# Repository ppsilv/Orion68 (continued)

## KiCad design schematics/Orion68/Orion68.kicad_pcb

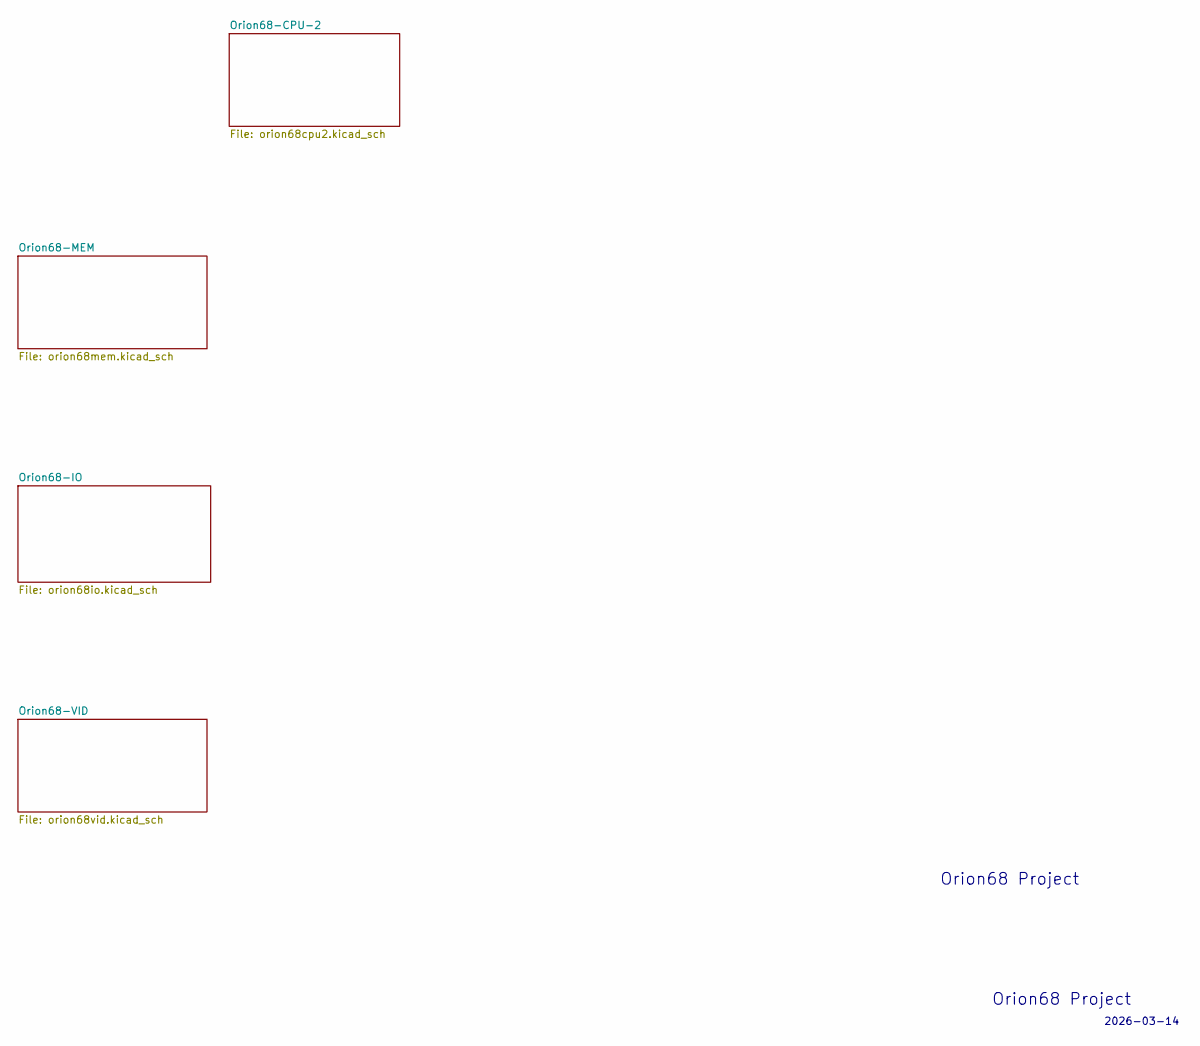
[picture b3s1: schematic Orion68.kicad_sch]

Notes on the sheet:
2026-03-14
Orion68 Project

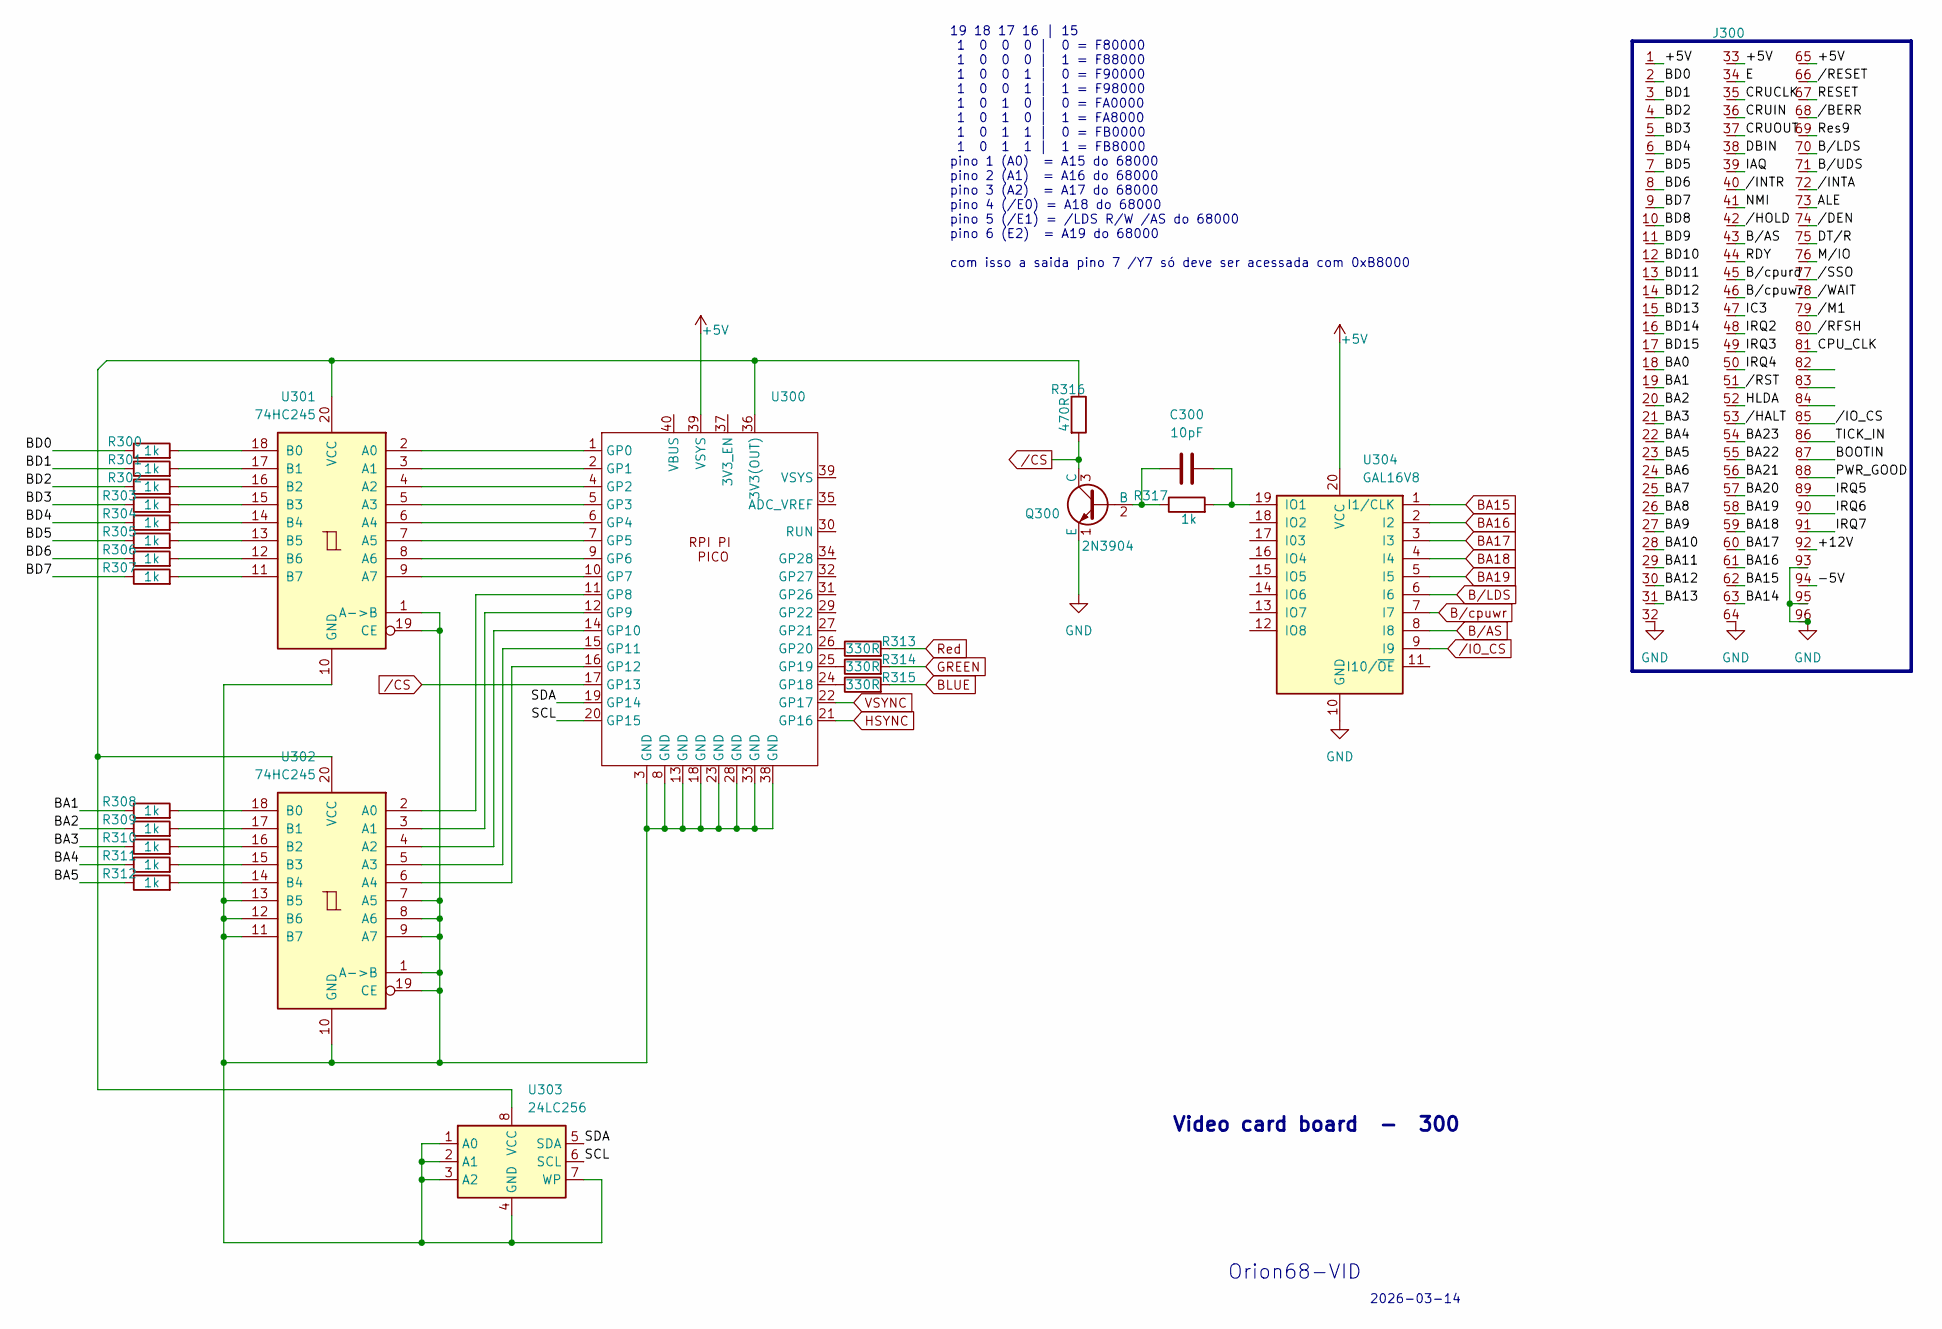
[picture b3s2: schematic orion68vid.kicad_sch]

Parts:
C300: 10pF; C_Disc_D4.3mm_W1.9mm_P5.00mm
J300: Euro96pin; conn_euro96
Q300: 2N3904; TO-92_Inline
R300, R301, R302, R303, R304, R305, R306, R307, R308, R309, R310, R311, R312, R317: 1k; R_Axial_DIN0204_L3.6mm_D1.6mm_P5.08mm_Horizontal
R313, R314, R315: 330R; R_Axial_DIN0204_L3.6mm_D1.6mm_P5.08mm_Horizontal
R316: 470R; R_Axial_DIN0204_L3.6mm_D1.6mm_P5.08mm_Horizontal
U300: DIP-40_W15.24mm
U301, U302: 74HC245; DIP-20_W7.62mm
U303: 24LC256; DIP-8_W7.62mm
U304: GAL16V8; DIP-20_W7.62mm

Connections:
+5V: J300.1, J300.33, J300.65, U300.39 (VSYS), U304.20 (VCC); also elsewhere on the board
/Orion68-VID/+12V: J300.92
/Orion68-VID/-5V: J300.94
/Orion68-VID/ALE: J300.73
/Orion68-VID/BA0: J300.18
/Orion68-VID/BA1: J300.19, R308.1
/Orion68-VID/BA2: J300.20, R309.1
/Orion68-VID/BA3: J300.21, R310.1
/Orion68-VID/BA4: J300.22, R311.1
/Orion68-VID/BA5: J300.23, R312.1
/Orion68-VID/BA6: J300.24
/Orion68-VID/BA7: J300.25
/Orion68-VID/BA8: J300.26
/Orion68-VID/BA9: J300.27
/Orion68-VID/BA10: J300.28
/Orion68-VID/BA11: J300.29
/Orion68-VID/BA12: J300.30
/Orion68-VID/BA13: J300.31
/Orion68-VID/BA14: J300.63
/Orion68-VID/BA20: J300.57
/Orion68-VID/BA21: J300.56
/Orion68-VID/BA22: J300.55
/Orion68-VID/BA23: J300.54
/Orion68-VID/BD0: J300.2, R300.1
/Orion68-VID/BD1: J300.3, R301.1
/Orion68-VID/BD2: J300.4, R302.1
/Orion68-VID/BD3: J300.5, R303.1
/Orion68-VID/BD4: J300.6, R304.1
/Orion68-VID/BD5: J300.7, R305.1
/Orion68-VID/BD6: J300.8, R306.1
/Orion68-VID/BD7: J300.9, R307.1
/Orion68-VID/BD8: J300.10
/Orion68-VID/BD9: J300.11
/Orion68-VID/BD10: J300.12
/Orion68-VID/BD11: J300.13
/Orion68-VID/BD12: J300.14
/Orion68-VID/BD13: J300.15
/Orion68-VID/BD14: J300.16
/Orion68-VID/BD15: J300.17
/Orion68-VID/BOOTIN: J300.87
/Orion68-VID/B/UDS: J300.71
/Orion68-VID/B/cpurd: J300.45
/Orion68-VID/CPU_CLK: J300.81
/Orion68-VID/CRUCLK: J300.35
/Orion68-VID/CRUIN: J300.36
/Orion68-VID/CRUOUT: J300.37
/Orion68-VID/DBIN: J300.38
/Orion68-VID/DT/R: J300.75
/Orion68-VID/E: J300.34
/Orion68-VID/HLDA: J300.52
/Orion68-VID/IAQ: J300.39
/Orion68-VID/IC3: J300.47
/Orion68-VID/IRQ2: J300.48
/Orion68-VID/IRQ3: J300.49
/Orion68-VID/IRQ4: J300.50
/Orion68-VID/IRQ5: J300.89
/Orion68-VID/IRQ6: J300.90
/Orion68-VID/IRQ7: J300.91
/Orion68-VID/M/IO: J300.76
/Orion68-VID/NMI: J300.41
/Orion68-VID/PWR_GOOD: J300.88
/Orion68-VID/RDY: J300.44
/Orion68-VID/RESET: J300.67
/Orion68-VID/Res9: J300.69
/Orion68-VID/SCL: U300.20 (GP15), U303.6 (SCL)
/Orion68-VID/SDA: U300.19 (GP14), U303.5 (SDA)
/Orion68-VID/TICK_IN: J300.86
/Orion68-VID//BERR: J300.68
/Orion68-VID//DEN: J300.74
/Orion68-VID//HALT: J300.53
/Orion68-VID//HOLD: J300.42
/Orion68-VID//INTA: J300.72
/Orion68-VID//INTR: J300.40
/Orion68-VID//M1: J300.79
/Orion68-VID//RESET: J300.66
/Orion68-VID//RFSH: J300.80
/Orion68-VID//RST: J300.51
/Orion68-VID//SSO: J300.77
/Orion68-VID//WAIT: J300.78
BA15: J300.62, U304.1 (I1/CLK)
BA16: J300.61, U304.2 (I2)
BA17: J300.60, U304.3 (I3)
BA18: J300.59, U304.4 (I4)
BA19: J300.58, U304.5 (I5)
BLUE: R315.2
B/AS: J300.43, U304.8 (I8)
B/LDS: J300.70, U304.6 (I6)
B/cpuwr: J300.46, U304.7 (I7)
GND: J300.32, J300.64, J300.93, J300.95, J300.96, Q300.1 (E), U304.10 (GND); also elsewhere on the board
GREEN: R314.2
HSYNC: U300.21 (GP16)
unnamed: C300.1, Q300.2 (B), R317.1
unnamed: R316.1, U300.36 (3V3(OUT)), U301.20 (VCC), U302.20 (VCC), U303.8 (VCC)
unnamed: U300.1 (GP0), U301.2 (A0)
unnamed: U300.2 (GP1), U301.3 (A1)
unnamed: U300.4 (GP2), U301.4 (A2)
unnamed: U300.5 (GP3), U301.5 (A3)
unnamed: U300.6 (GP4), U301.6 (A4)
unnamed: U300.7 (GP5), U301.7 (A5)
unnamed: U300.9 (GP6), U301.8 (A6)
unnamed: U300.10 (GP7), U301.9 (A7)
unnamed: U300.11 (GP8), U302.2 (A0)
unnamed: U300.12 (GP9), U302.3 (A1)
unnamed: U300.14 (GP10), U302.4 (A2)
unnamed: U300.15 (GP11), U302.5 (A3)
unnamed: U300.16 (GP12), U302.6 (A4)
unnamed: R315.1, U300.24 (GP18)
unnamed: R314.1, U300.25 (GP19)
unnamed: R313.1, U300.26 (GP20)
unnamed: U300.3 (GND), U300.8 (GND), U300.13 (GND), U300.18 (GND), U300.23 (GND), U300.28 (GND), U300.33 (GND), U300.38 (GND), U301.1 (A->B), U301.10 (GND), U301.19 (CE), U302.1 (A->B), U302.7 (A5), U302.8 (A6), U302.9 (A7), U302.10 (GND), U302.11 (B7), U302.12 (B6), U302.13 (B5), U302.19 (CE), U303.1 (A0), U303.2 (A1), U303.3 (A2), U303.4 (GND), U303.7 (WP)
unnamed: R300.2, U301.18 (B0)
unnamed: R301.2, U301.17 (B1)
unnamed: R302.2, U301.16 (B2)
unnamed: R303.2, U301.15 (B3)
unnamed: R304.2, U301.14 (B4)
unnamed: R305.2, U301.13 (B5)
unnamed: R306.2, U301.12 (B6)
unnamed: R307.2, U301.11 (B7)
unnamed: R308.2, U302.18 (B0)
unnamed: R309.2, U302.17 (B1)
unnamed: R310.2, U302.16 (B2)
unnamed: R311.2, U302.15 (B3)
unnamed: R312.2, U302.14 (B4)
unnamed: C300.2, R317.2, U304.19 (IO1)
Red: R313.2
VSYNC: U300.22 (GP17)
/CS: Q300.3 (C), R316.2, U300.17 (GP13)
/IO_CS: J300.85, U304.9 (I9)

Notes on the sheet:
2026-03-14
19 18 17 16 | 15 1 0 0 0 | 0 = F80000 1 0 0 0 | 1 = F88000 1 0 0 1 | 0 = F90000 1 0 0 1 | 1 = F98000 1 0 1 0 | 0 = FA0000 1 0 1 0 | 1 = FA8000 1 0 1 1 | 0 = FB0000 1 0 1 1 | 1 = FB8000 pino 1 (A0) = A15 do 68000 pino 2 (A1) = A16 do 68000 pino 3 (A2) = A17 do 68000 pino 4 (/E0) = A18 do 68000 pino 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
Orion68-VID
Video card board - 300

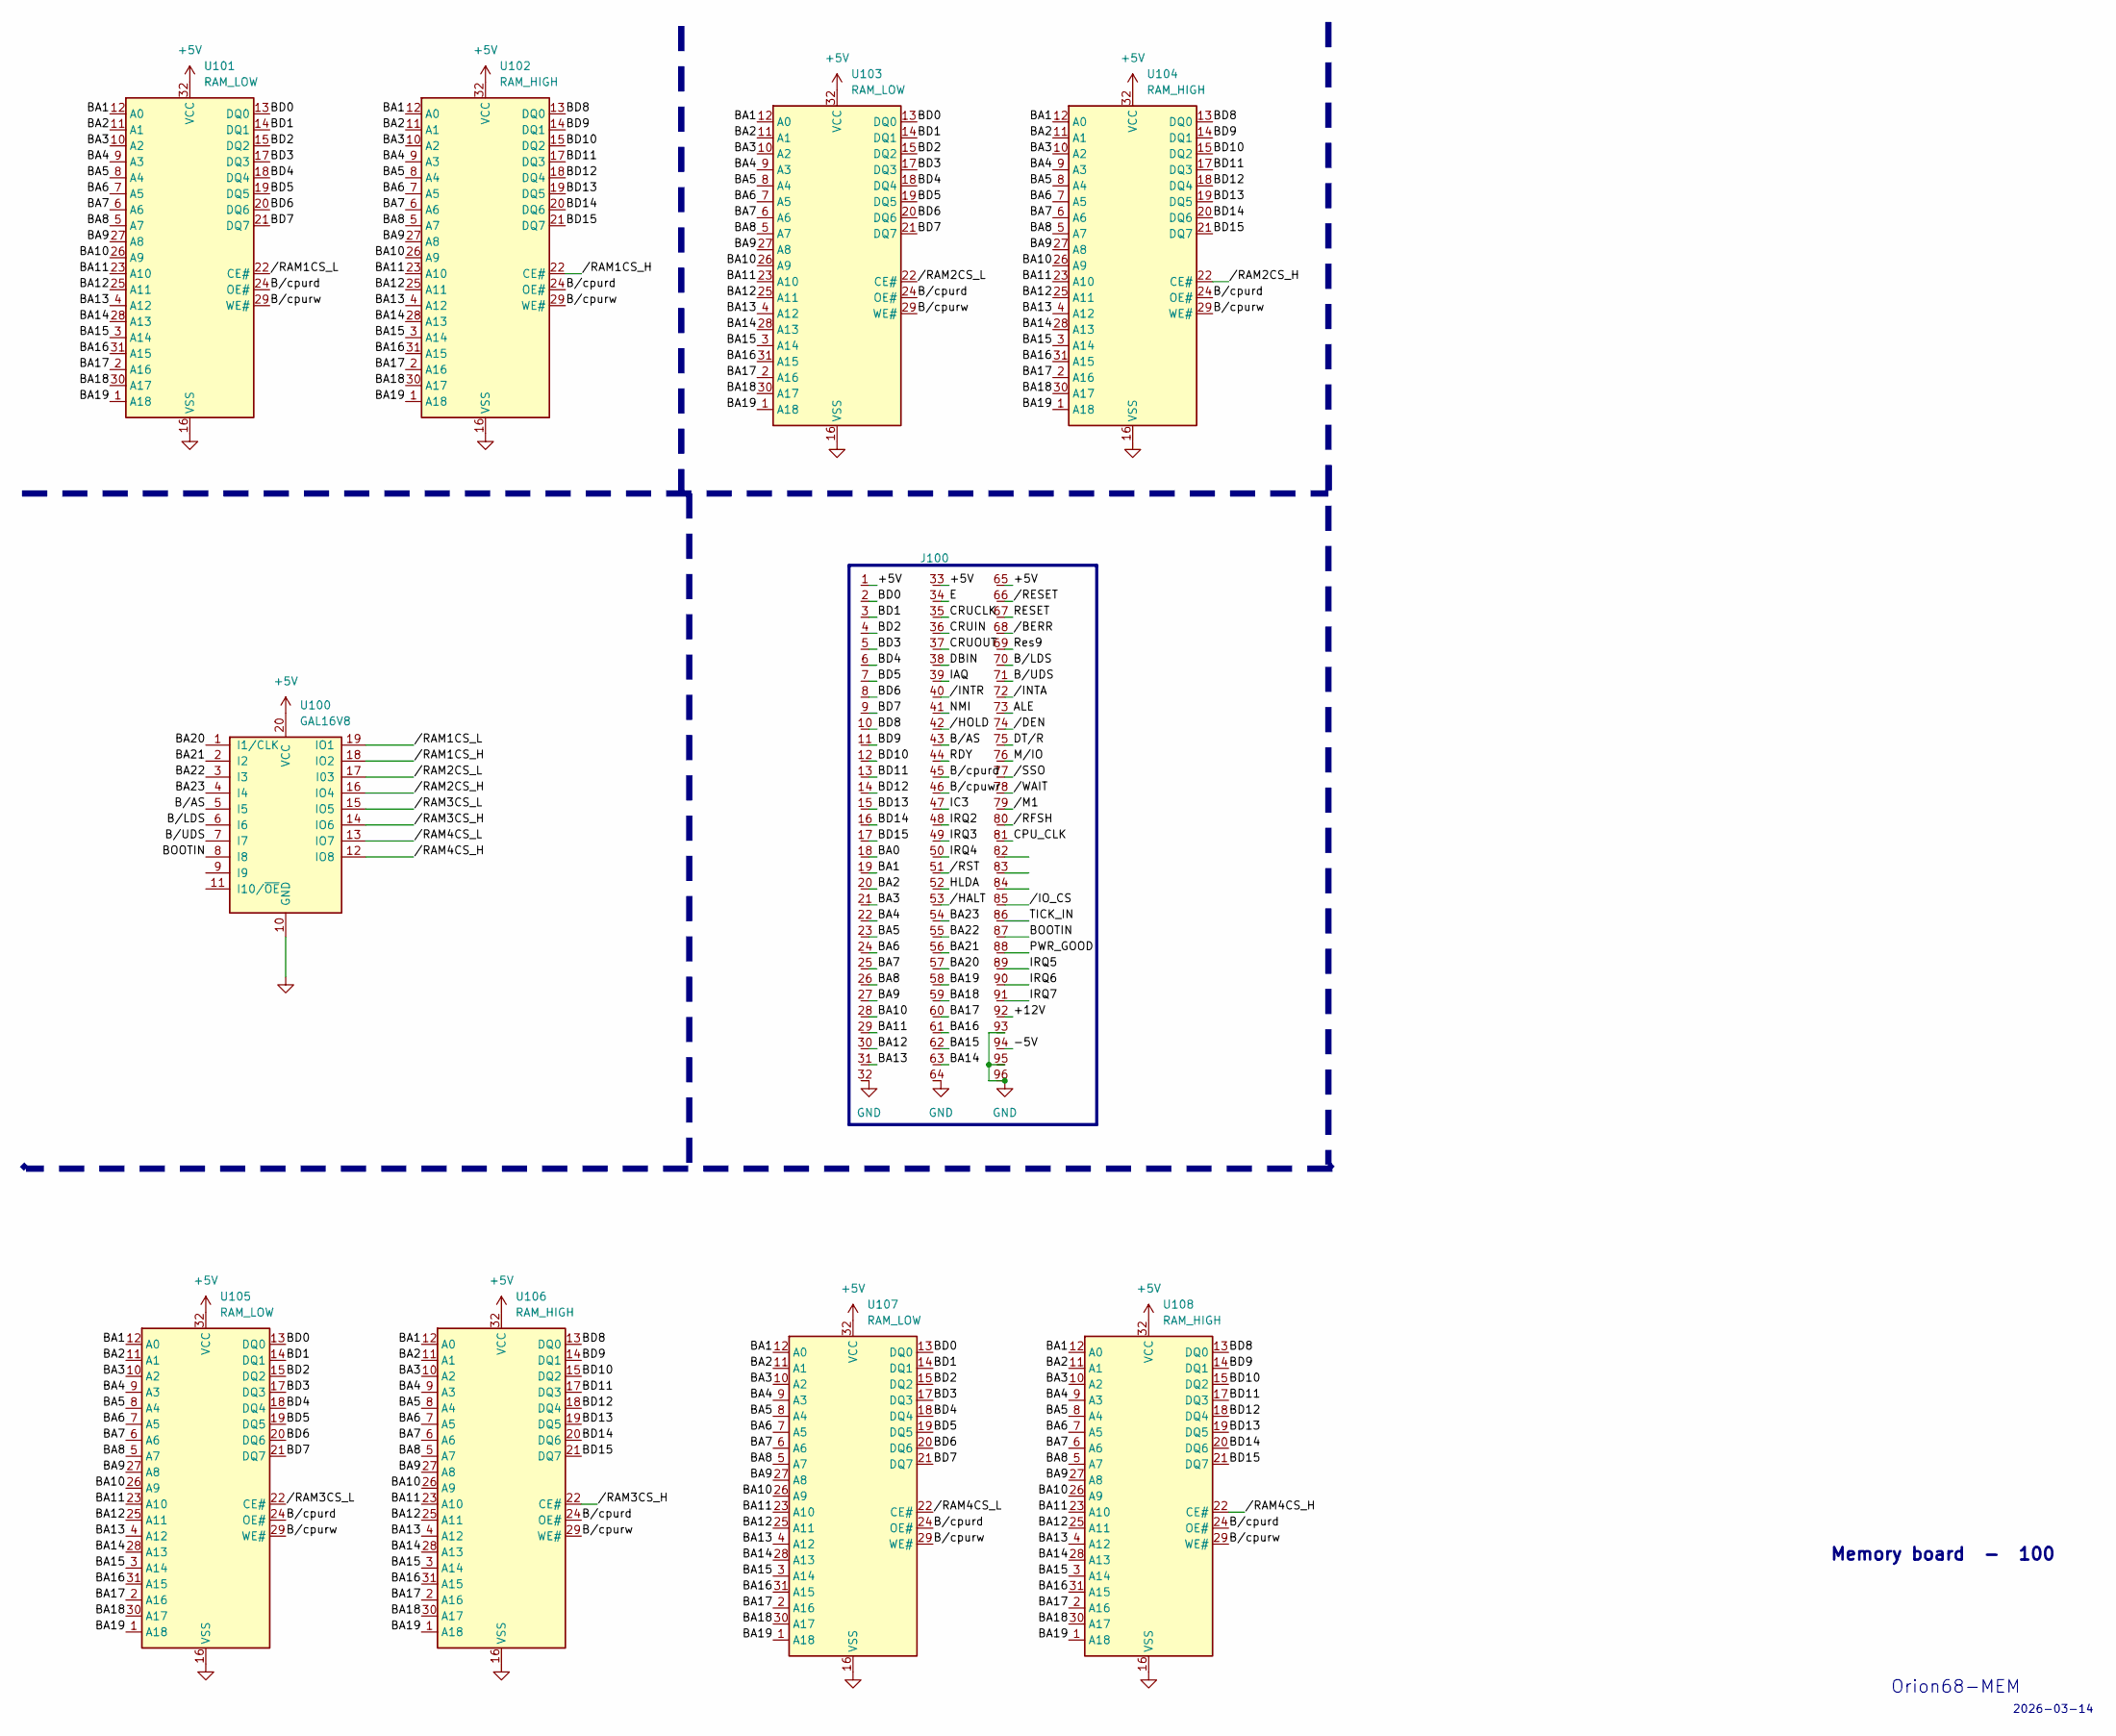
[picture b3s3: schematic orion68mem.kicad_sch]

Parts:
J100: Euro96pin; conn_euro96
U100: GAL16V8; DIP-20_W7.62mm
U101, U103, U105, U107: RAM_LOW; DIP-32_W15.24mm
U102, U104, U106, U108: RAM_HIGH; DIP-32_W15.24mm

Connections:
+5V: J100.1, J100.33, J100.65, U100.20 (VCC), U101.32 (VCC), U102.32 (VCC), U103.32 (VCC), U104.32 (VCC), U105.32 (VCC), U106.32 (VCC), U107.32 (VCC), U108.32 (VCC); also elsewhere on the board
/Orion68-MEM/+12V: J100.92
/Orion68-MEM/-5V: J100.94
/Orion68-MEM/ALE: J100.73
/Orion68-MEM/BA0: J100.18
/Orion68-MEM/BA1: J100.19, U101.12 (A0), U102.12 (A0), U103.12 (A0), U104.12 (A0), U105.12 (A0), U106.12 (A0), U107.12 (A0), U108.12 (A0)
/Orion68-MEM/BA2: J100.20, U101.11 (A1), U102.11 (A1), U103.11 (A1), U104.11 (A1), U105.11 (A1), U106.11 (A1), U107.11 (A1), U108.11 (A1)
/Orion68-MEM/BA3: J100.21, U101.10 (A2), U102.10 (A2), U103.10 (A2), U104.10 (A2), U105.10 (A2), U106.10 (A2), U107.10 (A2), U108.10 (A2)
/Orion68-MEM/BA4: J100.22, U101.9 (A3), U102.9 (A3), U103.9 (A3), U104.9 (A3), U105.9 (A3), U106.9 (A3), U107.9 (A3), U108.9 (A3)
/Orion68-MEM/BA5: J100.23, U101.8 (A4), U102.8 (A4), U103.8 (A4), U104.8 (A4), U105.8 (A4), U106.8 (A4), U107.8 (A4), U108.8 (A4)
/Orion68-MEM/BA6: J100.24, U101.7 (A5), U102.7 (A5), U103.7 (A5), U104.7 (A5), U105.7 (A5), U106.7 (A5), U107.7 (A5), U108.7 (A5)
/Orion68-MEM/BA7: J100.25, U101.6 (A6), U102.6 (A6), U103.6 (A6), U104.6 (A6), U105.6 (A6), U106.6 (A6), U107.6 (A6), U108.6 (A6)
/Orion68-MEM/BA8: J100.26, U101.5 (A7), U102.5 (A7), U103.5 (A7), U104.5 (A7), U105.5 (A7), U106.5 (A7), U107.5 (A7), U108.5 (A7)
/Orion68-MEM/BA9: J100.27, U101.27 (A8), U102.27 (A8), U103.27 (A8), U104.27 (A8), U105.27 (A8), U106.27 (A8), U107.27 (A8), U108.27 (A8)
/Orion68-MEM/BA10: J100.28, U101.26 (A9), U102.26 (A9), U103.26 (A9), U104.26 (A9), U105.26 (A9), U106.26 (A9), U107.26 (A9), U108.26 (A9)
/Orion68-MEM/BA11: J100.29, U101.23 (A10), U102.23 (A10), U103.23 (A10), U104.23 (A10), U105.23 (A10), U106.23 (A10), U107.23 (A10), U108.23 (A10)
/Orion68-MEM/BA12: J100.30, U101.25 (A11), U102.25 (A11), U103.25 (A11), U104.25 (A11), U105.25 (A11), U106.25 (A11), U107.25 (A11), U108.25 (A11)
/Orion68-MEM/BA13: J100.31, U101.4 (A12), U102.4 (A12), U103.4 (A12), U104.4 (A12), U105.4 (A12), U106.4 (A12), U107.4 (A12), U108.4 (A12)
/Orion68-MEM/BA14: J100.63, U101.28 (A13), U102.28 (A13), U103.28 (A13), U104.28 (A13), U105.28 (A13), U106.28 (A13), U107.28 (A13), U108.28 (A13)
/Orion68-MEM/BA15: J100.62, U101.3 (A14), U102.3 (A14), U103.3 (A14), U104.3 (A14), U105.3 (A14), U106.3 (A14), U107.3 (A14), U108.3 (A14)
/Orion68-MEM/BA16: J100.61, U101.31 (A15), U102.31 (A15), U103.31 (A15), U104.31 (A15), U105.31 (A15), U106.31 (A15), U107.31 (A15), U108.31 (A15)
/Orion68-MEM/BA17: J100.60, U101.2 (A16), U102.2 (A16), U103.2 (A16), U104.2 (A16), U105.2 (A16), U106.2 (A16), U107.2 (A16), U108.2 (A16)
/Orion68-MEM/BA18: J100.59, U101.30 (A17), U102.30 (A17), U103.30 (A17), U104.30 (A17), U105.30 (A17), U106.30 (A17), U107.30 (A17), U108.30 (A17)
/Orion68-MEM/BA19: J100.58, U101.1 (A18), U102.1 (A18), U103.1 (A18), U104.1 (A18), U105.1 (A18), U106.1 (A18), U107.1 (A18), U108.1 (A18)
/Orion68-MEM/BA20: J100.57, U100.1 (I1/CLK)
/Orion68-MEM/BA21: J100.56, U100.2 (I2)
/Orion68-MEM/BA22: J100.55, U100.3 (I3)
/Orion68-MEM/BA23: J100.54, U100.4 (I4)
/Orion68-MEM/BD0: J100.2, U101.13 (DQ0), U103.13 (DQ0), U105.13 (DQ0), U107.13 (DQ0)
/Orion68-MEM/BD1: J100.3, U101.14 (DQ1), U103.14 (DQ1), U105.14 (DQ1), U107.14 (DQ1)
/Orion68-MEM/BD2: J100.4, U101.15 (DQ2), U103.15 (DQ2), U105.15 (DQ2), U107.15 (DQ2)
/Orion68-MEM/BD3: J100.5, U101.17 (DQ3), U103.17 (DQ3), U105.17 (DQ3), U107.17 (DQ3)
/Orion68-MEM/BD4: J100.6, U101.18 (DQ4), U103.18 (DQ4), U105.18 (DQ4), U107.18 (DQ4)
/Orion68-MEM/BD5: J100.7, U101.19 (DQ5), U103.19 (DQ5), U105.19 (DQ5), U107.19 (DQ5)
/Orion68-MEM/BD6: J100.8, U101.20 (DQ6), U103.20 (DQ6), U105.20 (DQ6), U107.20 (DQ6)
/Orion68-MEM/BD7: J100.9, U101.21 (DQ7), U103.21 (DQ7), U105.21 (DQ7), U107.21 (DQ7)
/Orion68-MEM/BD8: J100.10, U102.13 (DQ0), U104.13 (DQ0), U106.13 (DQ0), U108.13 (DQ0)
/Orion68-MEM/BD9: J100.11, U102.14 (DQ1), U104.14 (DQ1), U106.14 (DQ1), U108.14 (DQ1)
/Orion68-MEM/BD10: J100.12, U102.15 (DQ2), U104.15 (DQ2), U106.15 (DQ2), U108.15 (DQ2)
/Orion68-MEM/BD11: J100.13, U102.17 (DQ3), U104.17 (DQ3), U106.17 (DQ3), U108.17 (DQ3)
/Orion68-MEM/BD12: J100.14, U102.18 (DQ4), U104.18 (DQ4), U106.18 (DQ4), U108.18 (DQ4)
/Orion68-MEM/BD13: J100.15, U102.19 (DQ5), U104.19 (DQ5), U106.19 (DQ5), U108.19 (DQ5)
/Orion68-MEM/BD14: J100.16, U102.20 (DQ6), U104.20 (DQ6), U106.20 (DQ6), U108.20 (DQ6)
/Orion68-MEM/BD15: J100.17, U102.21 (DQ7), U104.21 (DQ7), U106.21 (DQ7), U108.21 (DQ7)
/Orion68-MEM/BOOTIN: J100.87, U100.8 (I8)
/Orion68-MEM/B/AS: J100.43, U100.5 (I5)
/Orion68-MEM/B/LDS: J100.70, U100.6 (I6)
/Orion68-MEM/B/UDS: J100.71, U100.7 (I7)
/Orion68-MEM/B/cpurd: J100.45, U101.24 (OE#), U102.24 (OE#), U103.24 (OE#), U104.24 (OE#), U105.24 (OE#), U106.24 (OE#), U107.24 (OE#), U108.24 (OE#)
/Orion68-MEM/B/cpurw: U101.29 (WE#), U102.29 (WE#), U103.29 (WE#), U104.29 (WE#), U105.29 (WE#), U106.29 (WE#), U107.29 (WE#), U108.29 (WE#)
/Orion68-MEM/B/cpuwr: J100.46
/Orion68-MEM/CPU_CLK: J100.81
/Orion68-MEM/CRUCLK: J100.35
/Orion68-MEM/CRUIN: J100.36
/Orion68-MEM/CRUOUT: J100.37
/Orion68-MEM/DBIN: J100.38
/Orion68-MEM/DT/R: J100.75
/Orion68-MEM/E: J100.34
/Orion68-MEM/HLDA: J100.52
/Orion68-MEM/IAQ: J100.39
/Orion68-MEM/IC3: J100.47
/Orion68-MEM/IRQ2: J100.48
/Orion68-MEM/IRQ3: J100.49
/Orion68-MEM/IRQ4: J100.50
/Orion68-MEM/IRQ5: J100.89
/Orion68-MEM/IRQ6: J100.90
/Orion68-MEM/IRQ7: J100.91
/Orion68-MEM/M/IO: J100.76
/Orion68-MEM/NMI: J100.41
/Orion68-MEM/PWR_GOOD: J100.88
/Orion68-MEM/RDY: J100.44
/Orion68-MEM/RESET: J100.67
/Orion68-MEM/Res9: J100.69
/Orion68-MEM/TICK_IN: J100.86
/Orion68-MEM//BERR: J100.68
/Orion68-MEM//DEN: J100.74
/Orion68-MEM//HALT: J100.53
/Orion68-MEM//HOLD: J100.42
/Orion68-MEM//INTA: J100.72
/Orion68-MEM//INTR: J100.40
/Orion68-MEM//IO_CS: J100.85
/Orion68-MEM//M1: J100.79
/Orion68-MEM//RAM1CS_H: U100.18 (IO2), U102.22 (CE#)
/Orion68-MEM//RAM1CS_L: U100.19 (IO1), U101.22 (CE#)
/Orion68-MEM//RAM2CS_H: U100.16 (IO4), U104.22 (CE#)
/Orion68-MEM//RAM2CS_L: U100.17 (I03), U103.22 (CE#)
/Orion68-MEM//RAM3CS_H: U100.14 (IO6), U106.22 (CE#)
/Orion68-MEM//RAM3CS_L: U100.15 (IO5), U105.22 (CE#)
/Orion68-MEM//RAM4CS_H: U100.12 (IO8), U108.22 (CE#)
/Orion68-MEM//RAM4CS_L: U100.13 (IO7), U107.22 (CE#)
/Orion68-MEM//RESET: J100.66
/Orion68-MEM//RFSH: J100.80
/Orion68-MEM//RST: J100.51
/Orion68-MEM//SSO: J100.77
/Orion68-MEM//WAIT: J100.78
GND: J100.32, J100.64, J100.93, J100.95, J100.96, U100.10 (GND), U101.16 (VSS), U102.16 (VSS), U103.16 (VSS), U104.16 (VSS), U105.16 (VSS), U106.16 (VSS), U107.16 (VSS), U108.16 (VSS); also elsewhere on the board

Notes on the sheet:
Orion68-MEM
Memory board - 100
2026-03-14

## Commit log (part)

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2026-03-14 Enhance README with project details and specifications
    Expanded the README to include detailed architecture, current hardware specifications, expansion boards, project goals, and status updates.
2026-03-14 Add documentation for Orion68 hobby computer
    Added detailed documentation for the Orion68 modular hobby computer, including features, hardware overview, system architecture, board types, current status, project goals, repository contents, and l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
2026-03-14 Add initial memory map documentation for Motorola 68000
    Documented the initial memory map for the Motorola 68000 architecture, including ROM, SRAM, I/O space, and future expansion areas.
2026-04-02 Finished CPU board schematic
2026-04-03 changed 68k dip for plcc
2026-04-04 updating
2026-04-09 Keyboard tested,code durty
2026-04-09 Updating cpu
2026-04-18 First cpu test
2026-04-23 Schematics update
2026-04-25 Schematic update
2026-04-28 Schematic verified to board
2026-05-01 Cpu board fixed and running
2026-05-04 New cpu board with NMOS running
2026-05-04 Updating...
2026-05-07 A20 bug fixed, missing serial CSA, running ok
2026-05-12 B column DIN conn. all in GND
2026-05-12 D0-D7 pull-ups 1K
2026-05-14 just update
2026-05-16 Update vbug2.0 80%
2026-05-16 added card vga pico2,env68k,atmega8
2026-05-17 New code for VBug2.0 with new reset system
2026-05-17 Running smoothly
2026-05-17 VBug2-0 began running ok...
2026-05-17 VBug2-0 began running ok...17 20:42
2026-05-18 Fixed buf do picoVGA clrscr() in 1920bytes,now running ok...18 17:07
2026-05-18 Trap #1 running ok...18 18:37
2026-05-18 Implemented VPA answer for interrupt running ok...18 20:12
2026-05-19 dump memory fixed stack leack...18 22:12
2026-05-21 Added drv_keboard
2026-05-25 finally VBUG2.0 running ok
2026-05-25 Sem duplicatas de entrada e saida de caractere
2026-05-26 Xmodem developing
2026-05-26 xmodem check sum implemented and working
2026-05-26 VBug2.0 with trap #1 ok runninf from C program hello
2026-05-27 keyboard start to run
2026-05-28 keyboard tested no production yet
2026-05-28 keyboard beta teste now
2026-05-28 keyboard beta tested now
2026-05-31 The begining of VBug2.1 in C
2026-05-31 Trap#1 cconout -> picoVga
2026-05-31 PicoVGA fixed
2026-06-01 Updated libmc68000.a
2026-06-01 fixed strtol libmc68000.a
2026-06-03 Teclado funcionando
2026-06-03 Working code...
2026-06-06 update 06/06
2026-06-07 xmodem running ok
2026-06-08 Implemented interrupted 2 for systick
2026-06-14 Implementation drive ide initiated
2026-06-14 ReAdded xmodem.c
2026-06-14 removed dir xmodem
2026-06-14 Readded xmodem
2026-06-14 deleted part.c
2026-06-14 Added divsi3,modsi3,mulsi3,udivsi3,umodsi3,umulsi3
2026-06-14 Working on fatfs compiled and added control ctrl
2026-06-16 Version 1.2 picoVGA implemented a workaround for the UART issue
2026-06-16 Version 1.2 picoVGA sem protothreads e com buffer para receber comandos
2026-06-16 Version 1.2 picoVGA sem delay por caractere
2026-06-18 Vbug2.0 rodando 18-06-2026
2026-06-20 PDS600 100% routed
2026-06-22 Finished PDS100 routing
2026-06-22 Added PDS100 board manual
2026-06-23 vbug2.2 alpha running
2026-06-24 get_char for kbd alpha 5 compila
2026-06-24 vbug2.2 alpha 4 running
2026-06-26 FatFs ChaN funcionando listando diretorio e listando conteudo de arquivo
2026-06-30 Orion68 OS compiled but not tested
